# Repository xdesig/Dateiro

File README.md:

# Dateiro - Datalogger e visualización

> [!NOTE]
> Documentation in Galego 
> [traductor](https://tradutorgaio.xunta.gal/TradutorPublico/traducir/index)

**Dateiro** e un sistema de adquisicion, visualizacion e rexistro de datos (datalogger) deseñado arredor do microcontrolador **ESP32-C3 SuperMini**.
O dispositivo permite a medicion de voltaxe diferencial, corrente e voltaxe de bus, mostrando un grafico en tempo real (modo osciloscopio) nunha pantalla e almacenando os datos en ficheiros `.CSV`
dentro duna tarxeta MicroSD.

---

## Caracteristicas do Firmware

### 1. Gráfica en Tempo Real
- **Buffer Circular:** Mantén un historico de 128 puntos para debuxar a onda na pantalla OLED a intervalos de 50ms (refresh de 20 Hz).
- **Escalado e Grade:** Debuxo de grade de puntos para escala visual e axuste automatico de rango (hasta 16V en modo diferencial e ata 1000mA en modo INA219).

### 2. Datalogger Automático (Ficheiros CSV)
- **Nomenclatura Automática:** Crea ficheiros secuenciais no directorio raiz da tarxeta SD (`/DAT_001.CSV`, `/DAT_002.CSV`, etc.).
- **Modos de Mostraxe:**
  - **Por Intervalo:** Define o tempo entre mostras en segundos (ex: cada 5s).
  - **Por Cantidade de Puntos:** Distribue un numero fixo de puntos ao longo do tempo total configurado.
- **Formato do CSV:** Encabezado dinamico dependendo da orixe de datos (`Tempo_ms,Diferencial_V` ou `Tempo_ms,Corrente_mA`).

### 3. Navegación
- Interface baseada nun **Encoder Rotatorio** con descodificacion por matriz de estados (anti-rebotes por interruptor de hardware/software).
- **Xestion de Clicks:**
  - **Click Curto (>50ms):** Confirmar / Avanzar menu.
  - **Click Longo (>600ms):** Voltar / Cancelar / Deter gravacion.
  - **Dobre Click (<400ms):** Menu de apagado rapido.

### 4. Xestión de Enerxía e Deep Sleep
- **Lendo Batería:** Indicador de bateria con icono grafico na barra superior calculando o nivel mediante o pin `MVBAT` e detectando se esta en carga polo pin `STAT`.
- **Modo Apagado (Deep Sleep):** Apaga a pantalla OLED mediante comandos I2C (`0xAE`) e pon o ESP32-C3 en modo de soño profundo, incluida a OLED.
- **Despertado por Hardware:** Configura o pin do encoder (`PIN_ENC_B` / GPIO5) para espertar o sistema ao xirar o mando.

---

## Asignación de Pins (ESP32-C3 SuperMini)

| GPIO | Rede / Sinal | Descricion |
| :---: | :--- | :--- |
| **GPIO0** | `MOSI` | Bus SPI (Tarxeta SD) |
| **GPIO1** | `MVBAT` | Medicion de voltaxe da Bateria (Factor 1.816) |
| **GPIO2** | `MISO` | Bus SPI (Tarxeta SD) |
| **GPIO3** | `CS` | Chip Select SPI (Tarxeta SD) |
| **GPIO4** | `MEDV` | Entrada Analoxica Amplificada (LMC7101) |
| **GPIO5** | `ENC_B` | Encoder Rotatorio - Canle B (Wakeup GPIO) |
| **GPIO6** | `REG_EN` | Habilitacion do Regulador de Tensión |
| **GPIO7** | `ENC_A` | Encoder Rotatorio - Canle A |
| **GPIO8** | `STAT` | Estado da carga de Bateria (MCP73831) |
| **GPIO9** | `ENC_S` | Pulsador do Encoder Rotatorio |
| **GPIO10**| `CLK` | Reloxo Bus SPI (Tarxeta SD) |
| **GPIO20**| `SDA` | Bus I2C (OLED SH1106 + INA219) |
| **GPIO21**| `SCL` | Bus I2C (OLED SH1106 + INA219) |

---

## Librarías Requiridas

Para compilar este proxecto na IDE de Arduino ou PlatformIO, precísanse as seguintes librarías:

- `Wire.h` e `SPI.h` (Incluídas no core de ESP32)
- `SD.h` (Incluída no core de ESP32)
- [Adafruit_GFX](https://github.com/adafruit/Adafruit-GFX-Library)
- [Adafruit_SH110X](https://github.com/adafruit/Adafruit_SH110X) (Para pantallas OLED SH1106G)
- [Adafruit_INA219](https://github.com/adafruit/Adafruit_INA219)

---

## Bill of Materials (BOM)

| Qty | Value / Component | Footprint / Package | Designator | Description |
| :---: | :--- | :--- | :--- | :--- |
| **2** | 10uF | C0603 | `C1`, `C3` | Capacitor |
| **1** | 100nF | C0603 | `C2` | Capacitor |
| **1** | SS14 | SOD-323 | `D1` | Diodo Schottky |
| **1** | Conn_01x02 | PinHeader 1x02 (2.54mm) | `J1` | Conector |
| **2** | Conn_01x04 | PinHeader 1x04 (2.54mm) | `J2`, `J3` | Conector |
| **1** | S8050 | SOT-23 | `Q1` | Transistor NPN |
| **4** | 10k | R0603 | `R1`, `R2`, `R4`, `R5` | Resistencia |
| **1** | 1k | R0603 | `R3` | Resistencia |
| **1** | SW_Push | 4.5x4.5mm | `SW1` | Pulsador |
| **1** | ESP32-C3-SuperMini | Board / Module | `U1` | Modulo Microcontrolador ESP32-C3 |
| **1** | HX711 | Module | `U2` | Modulo Amplificador Celula de Carga |
| **1** | DS1307 | SOP-8 | `U3` | Reloxo en Tempo Real (RTC) |
| **1** | 32.768kHz | Crystal D2.0mm L6.0mm | `Y1` | Cristal Oscilador RTC |

---
- Deseñado en Extrimia con agarimo.

- Saudos.

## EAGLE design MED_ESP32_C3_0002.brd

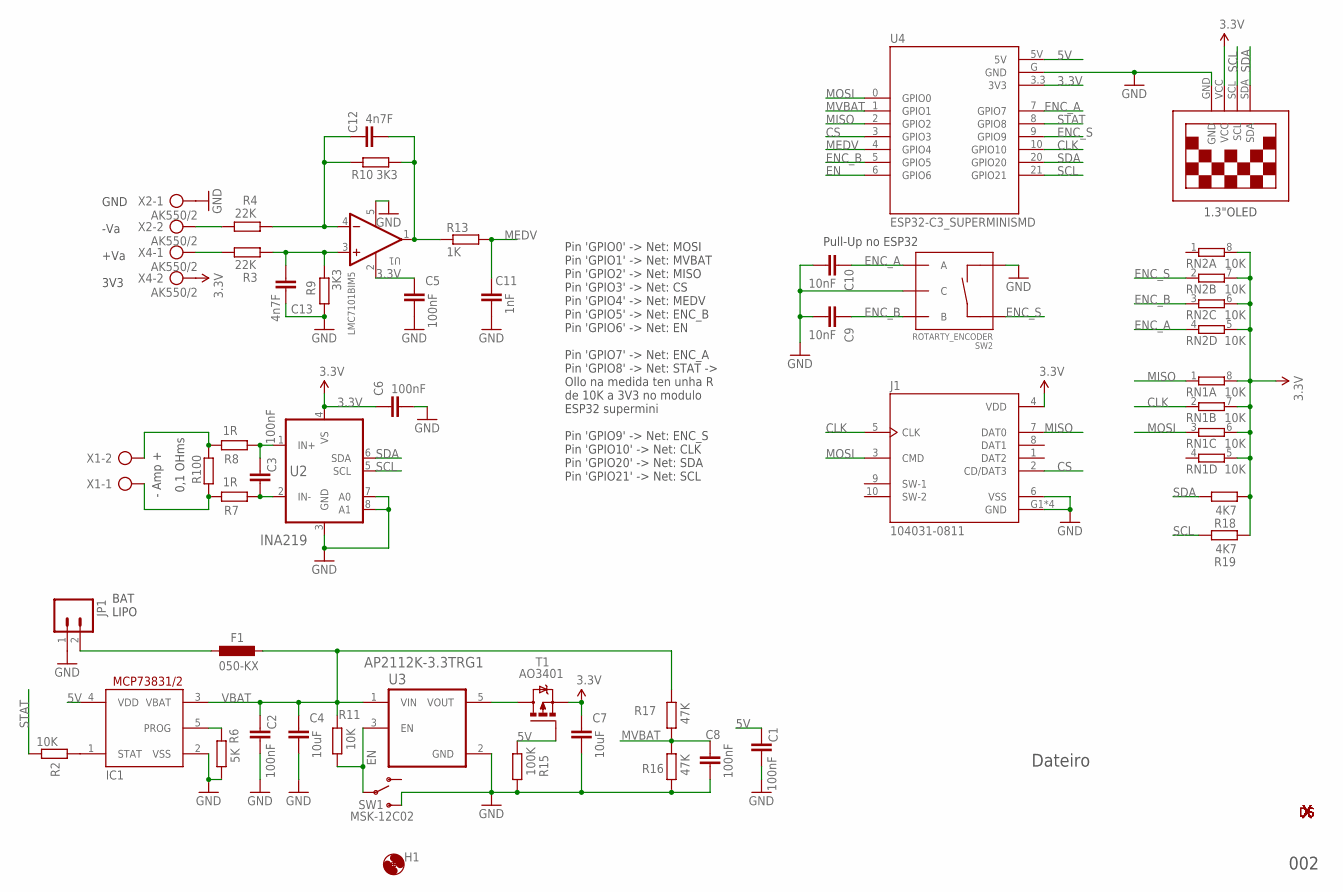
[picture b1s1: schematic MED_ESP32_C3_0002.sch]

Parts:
C1, C2, C3, C5, C6, C8: 100nF; C0603
C4, C7: 10uF; C1206
C9, C10: 10nF; C0603
C11: 1nF; C0603
C12, C13: 4n7F; C0603
F1: 050-KX; L3225M
H1: HOLES_MOUNT-HOLE3.2; HOLES_3,2
IC1: MCP73831T-2; SOT23-5L
J1: 104031-0811; MOLEX_104031-0811
JP1: M02JST-PTH-VERT; JST-2-PTH-VERT
R2, R11: 10K; R0603
R3, R4: 22K; R0603
R5: R100; R1210
R6: 5K; R0603
R7, R8: 1R; R0603
R9, R10: 3K3; R0603
R13: 1K; R0603
R15: 100K; R0603
R16, R17: 47K; R0603
R18, R19: 4K7; R0603
RN1: 10K; RESISTOR-DIL_0603-ARC
RN2: 10K; RESISTOR-DIL_0603-ARV
SW1: MSK-12C02; KPS-1290
SW2: ROTARTY_ENCODER; ROTARY_ENC_PLAIN
T1: AO3401; SOT23
U1: LMC7101BIM5; SOT95P280X145-5N
U2: INA219; SOT65P280X145-8N
U3: AP2112K-3.3TRG1; SOT95P285X140-5N
U4: ESP32-C3_SUPERMINISMD; MODULE_ESP-C3_SUPERMINI_SMD
U$1: 13"OLED13"OLED; 1.3"OLED
U$2, U$5: XDESIG5MM; XDESIG_CU
U$3, U$4: XDESIG21; XDESIG
X1: AK500/2
X2, X4: AK550/2

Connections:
3.3V: C5.2, C6.2, C7.2, J1.4 (VDD), R18.2, R19.2, RN1.5 (2), RN1.6 (2), RN1.7 (2), RN1.8 (2), RN2.5 (2), RN2.6 (2), RN2.7 (2), RN2.8 (2), T1.2 (S), U1.2 (V+), U2.4 (VS), U4.3.3 (3V3), U$1.VCC, X4.2
5V: C1.1, IC1.4 (VDD), R15.2, T1.1 (G), U4.5V
CLK: J1.5 (CLK), RN1.2 (1), U4.10 (GPIO10)
CS: J1.2 (CD/DAT3), U4.3 (GPIO3)
EN: R11.1, SW1.P, U3.3 (EN), U4.6 (GPIO6)
ENC_A: C10.2, RN2.4 (1), SW2.A, U4.7 (GPIO7)
ENC_B: C9.2, RN2.3 (1), SW2.B, U4.5 (GPIO5)
ENC_S: RN2.2 (1), SW2.SW+, U4.9 (GPIO9)
GND: C1.2, C2.2, C4.1, C5.1, C6.1, C7.1, C8.2, C9.1, C10.1, C11.1, C13.2, IC1.2 (VSS), J1.6 (VSS), J1.G1 (GND), J1.G2 (GND), J1.G3 (GND), J1.G4 (GND), JP1.1, R6.1, R9.2, R15.1, R16.1, SW1.S, SW2.C, SW2.SW-, U1.5 (V-), U2.3 (GND), U2.7 (A0), U2.8 (A1), U3.2 (GND), U4.G (GND), U$1.GND, X2.1
MEDV: C11.2, R13.2, U4.4 (GPIO4)
MISO: J1.7 (DAT0), RN1.1, U4.2 (GPIO2)
MOSI: J1.3 (CMD), RN1.3 (1), U4.0 (GPIO0)
MVBAT: C8.1, R16.2, R17.1, U4.1 (GPIO1)
unnamed: R4.2, X2.2
unnamed: T1.3 (D), U3.5 (VOUT)
unnamed: C12.2, R4.1, R10.2, U1.4 (-IN)
unnamed: R3.2, X4.1
unnamed: IC1.1 (STAT), R2.2
unnamed: IC1.5 (PROG), R6.2
unnamed: C12.1, R10.1, R13.1, U1.1 (OUT)
unnamed: F1.2, JP1.2
unnamed: C13.1, R3.1, R9.1, U1.3 (+IN)
unnamed: C3.1, R8.2, U2.1 (IN+)
unnamed: C3.2, R7.2, U2.2 (IN-)
unnamed: R5.2, R8.1, X1.2
unnamed: R5.1, R7.1, X1.1
SCL: R19.1, U2.5 (SCL), U4.21 (GPIO21), U$1.SCL
SDA: R18.1, U2.6 (SDA), U4.20 (GPIO20), U$1.SDA
STAT: R2.1, U4.8 (GPIO8)
VBAT: C2.1, C4.2, F1.1, IC1.3 (VBAT), R11.2, R17.2, U3.1 (VIN)

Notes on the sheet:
0,1 OHms
BAT LIPO
Pull-Up no ESP32
002
Dateiro
1.3"OLED
Pin 'GPIO0' -> Net: MOSI Pin 'GPIO1' -> Net: MVBAT Pin 'GPIO2' -> Net: MISO Pin 'GPIO3' -> Net: CS Pin 'GPIO4' -> Net: MEDV Pin 'GPIO5' -> Net: ENC_B Pin 'GPIO6' -> Net: EN Pin 'GPIO7' -> Net: ENC_A Pin 'GPIO8' -> Net: STAT -> Ollo na medida ten unha R de 10K a 3V3 no modulo ESP32 supermini Pin 'GP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
GND -Va +Va 3V3
- Amp +

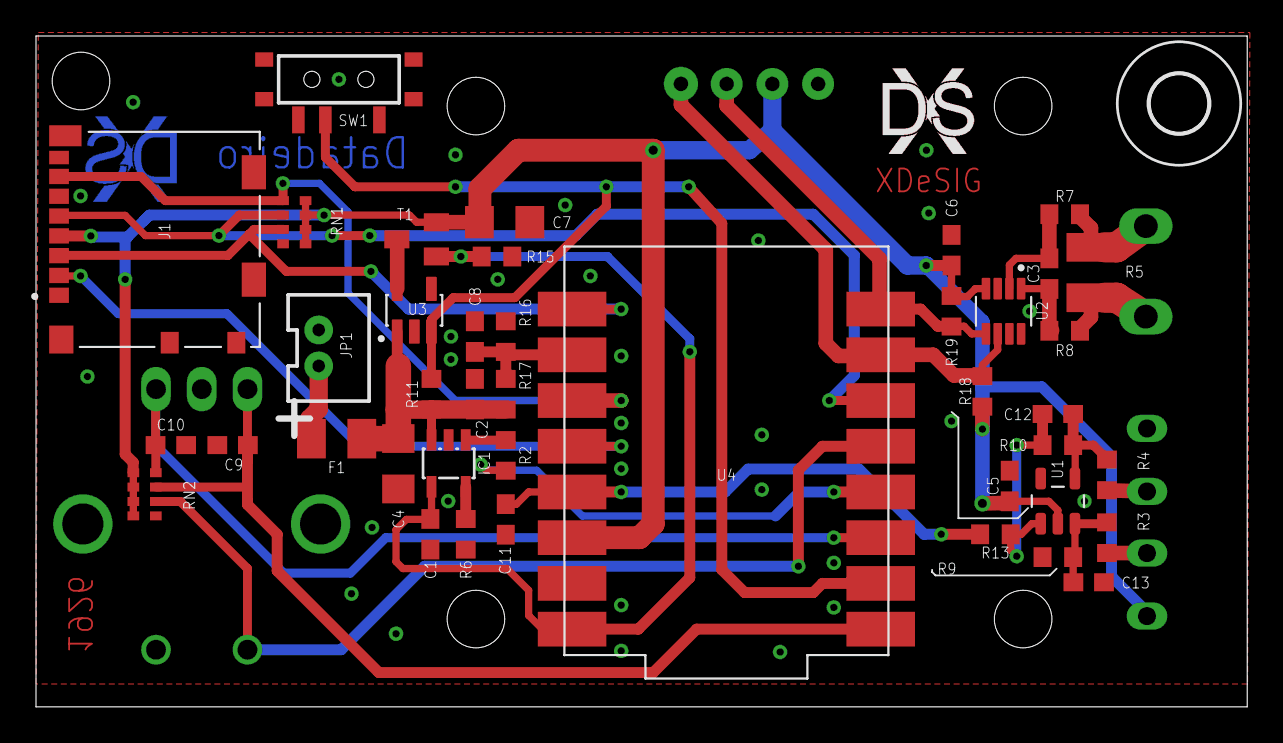
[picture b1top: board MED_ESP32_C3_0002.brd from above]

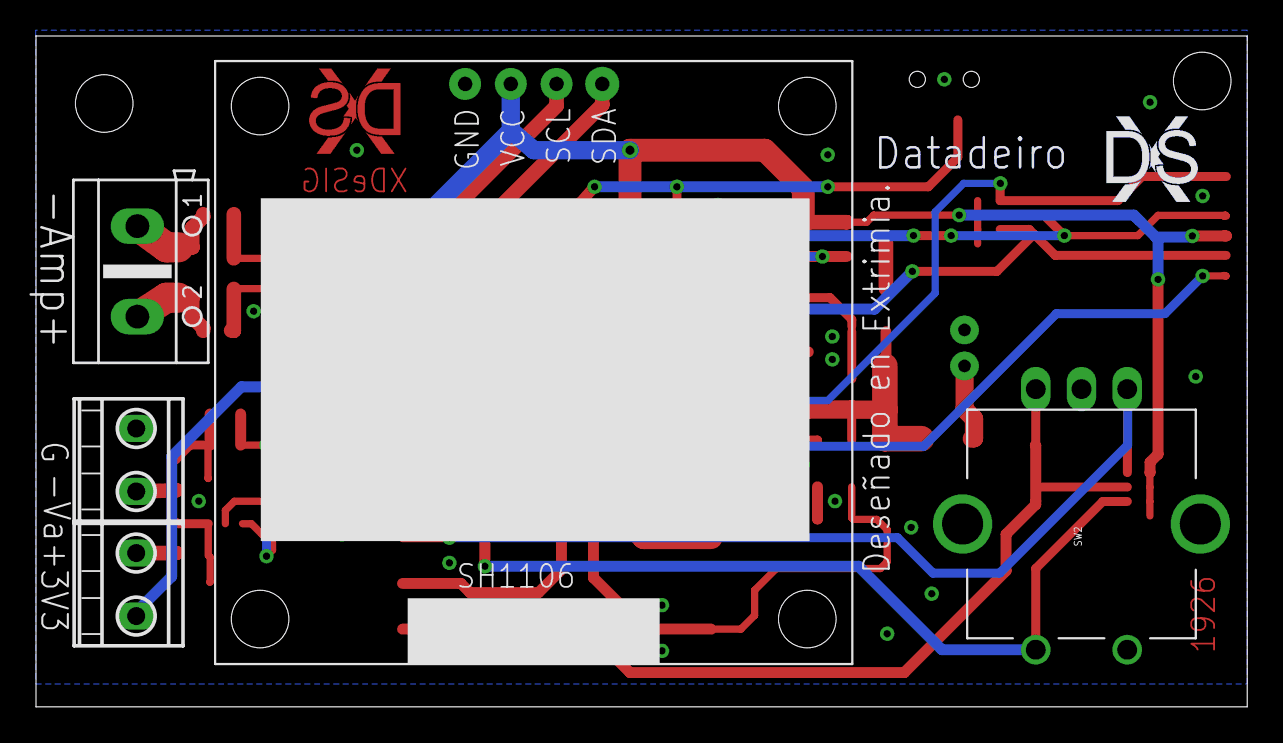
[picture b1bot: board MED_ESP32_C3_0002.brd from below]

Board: 2 copper layers, 67.3 x 37.3 mm, 51 parts (7 on the bottom side), 30 nets.

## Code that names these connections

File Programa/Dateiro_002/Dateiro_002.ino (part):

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
// --- DEFINICIÓN DE PINS ---
#define PIN_SD_MOSI   0
#define PIN_MVBAT     1  
#define PIN_SD_MISO   2
#define PIN_SD_CS     3
#define PIN_MEDV      4  
#define PIN_ENC_B     5
#define PIN_REG_EN    6
#define PIN_ENC_A     7
#define PIN_STAT      8
#define PIN_ENC_S     9  
#define PIN_SD_CLK    10
#define PIN_SDA_I2C   20
#define PIN_SCL_I2C   21
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
// --- INTERRUPCIÓN ENCODER ---
void IRAM_ATTR lerEncoder() {
  uint8_t pinstate = (digitalRead(PIN_ENC_A) << 1) | digitalRead(PIN_ENC_B);
  estadoEncoderSM = ttable[estadoEncoderSM & 0x0F][pinstate];
  uint8_t resultado = estadoEncoderSM & 0x30;
  
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  pinMode(PIN_REG_EN, OUTPUT);
  digitalWrite(PIN_REG_EN, HIGH); 
  
  pinMode(PIN_STAT, INPUT_PULLDOWN);
  pinMode(PIN_ENC_S, INPUT); 
  pinMode(PIN_ENC_A, INPUT);
  pinMode(PIN_ENC_B, INPUT);
  
  attachInterrupt(digitalPinToInterrupt(PIN_ENC_A), lerEncoder, CHANGE);
  attachInterrupt(digitalPinToInterrupt(PIN_ENC_B), lerEncoder, CHANGE);

  Wire.begin(PIN_SDA_I2C, PIN_SCL_I2C);
  Wire.setClock(400000);
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
void lerBoton() {
  clickCurto = false; clickLongo = false; dobreClick = false;
  bool estadoBotActual = digitalRead(PIN_ENC_S);
  uint32_t agora = millis();

  if (estadoBotAnterior == HIGH && estadoBotActual == LOW) t_press = agora;
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      
      float novoValor = 0.0;
      if (cfg_orixe == 0) { 
        int rawMedv = analogRead(PIN_MEDV);
        float vMedvLocal = (rawMedv * 3.3) / 4095.0;
        novoValor = (vMedvLocal - V_OFFSET_ZERO) / GANANCIA_REAL; 
        if(novoValor < 0) novoValor = 0;
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      Wire.endTransmission();
        
        // Creamos a máscara de bits para o GPIO 5 (1ULL << 5)
        uint64_t pin_mask = 1ULL << PIN_ENC_B; 
        
        // Activamos o espertar forzando o tipo de dato correcto para (LOW)
        // esperta o xirar o encoder
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
// *** Icono Bateria ***
void debuxarBateriaPequena(int x, int y) {
  int rawBat = analogRead(PIN_MVBAT);
  float vBat = ((rawBat * 3.3) / 4095.0) * FACTOR_CALIBRACION_BAT;
  bool cargando = (digitalRead(PIN_STAT) == LOW);
  
  pantalla.drawRect(x, y, 12, 7, SH110X_WHITE);
  pantalla.fillRect(x+12, y+2, 1, 3, SH110X_WHITE);
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

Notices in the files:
parts and their libraries:
SparkFun-Electromechanical: Licensing: Creative Commons ShareAlike 4.0 International - https://creativecommons.org/licenses/by-sa/4.0
